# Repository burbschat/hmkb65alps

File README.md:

# HMKB 65 Alps Compatible PCB and Plate
## Case
* HMKB V1 65 AAA by Heavymetal Keyboards

## Layout
Raw data for [keyboard-layout-editor.com](http://www.keyboard-layout-editor.com):
```json
["~\n`","!\n1","@\n2","#\n3","$\n4","%\n5","^\n6","&\n7","*\n8","(\n9",")\n0","_\n-","+\n=",{w:2},"Backspace",{a:7},""],
[{a:4,w:1.5},"Tab","Q","W","E","R","T","Y","U","I","O","P","{\n[","}\n]",{w:1.5},"|\n\\",{a:7},""],
[{a:4,w:1.75},"Caps Lock","A","S","D","F","G","H","J","K","L",":\n;","\"\n'",{w:2.25},"Enter",{a:7},""],
[{a:4,w:2.25},"Shift","Z","X","C","V","B","N","M","<\n,",">\n.","?\n/",{w:1.75},"Shift",{a:7},"",""],
[{a:4,w:1.25},"Ctrl",{w:1.25},"Win",{w:1.25},"Alt",{a:7,w:6.25},"",{a:4},"Alt","Fn","Ctrl",{a:7},"","",""] 
```
Matrix position annotated version (also without label position information as this messes with scripts using the annotated version down the line):
```json
["0,0","0,1","0,2","0,3","0,4","0,5","0,6","0,7","0,8","0,9","0,10","0,11","0,12",{w:2},"0,13","0,14"],
[{w:1.5},"1,0","1,1","1,2","1,3","1,4","1,5","1,6","1,7","1,8","1,9","1,10","1,11","1,12",{w:1.5},"1,13","1,14"],
[{w:1.75},"2,0","2,1","2,2","2,3","2,4","2,5","2,6","2,7","2,8","2,9","2,10","2,11",{w:2.25},"2,13","2,14"],
[{w:2.25},"3,0","3,1","3,2","3,3","3,4","3,5","3,6","3,7","3,8","3,9","3,10",{w:1.75},"3,12","3,13","3,14"],
[{w:1.25},"4,0",{w:1.25},"4,1",{w:1.25},"4,2",{w:6.25},"4,5","4,9","4,10","4,11","4,12","4,13","4,14"]
```

Find in proper json format in `hmkb65alps.json`.
The corresponding **annotated** (i.e. which key goes where in the matrix) in
[kle-serial](https://github.com/ijprest/kle-serial) format can be found in
`hmkb65alps-annotated_kle-serial.json` (converted using
[this](https://adamws.github.io/kle-serial/)).

## PCB

### Footprints etc.
Included as submodules in `lib/`. 
* [ai03-2725's MX_V2](https://github.com/ai03-2725/MX_V2) for switch footprints
* [ai03-2725's Type-C.pretty](https://github.com/ai03-2725/Type-C.pretty) for USB-C port footprints
* [ai03-2725's random-keyboard-parts.pretty](https://github.com/ai03-2725/random-keyboard-parts.pretty) for USB-C port footprints
The MX_V2 (which also contain ALPS footprints) are fine, the other ones are not
quite to my taste.

#### 3D Models for Key Switches
Found a ALPS switch model [here](https://www.thingiverse.com/thing:3829342/files). 
Very kindly there is an scad file provided (and not just a mesh `.stl` or similar)!

### Components
#### USB-C Connector
All of the options here are selected to be hand solderable.

`Korean Hroparts Elec TYPE-C-31-M-12` Seems to be a popular choice, probably because it's dirt cheap (<20cents).
However, it's not available on DigiKey, Mouser or RS. 

`GCT` offers a series of hand solderable connectors.
[Compare them here](https://gct.co/product-compare/usb/usb4085,usb4105,usb4730,usb4800,usb4215).
Note that `USB4085` is entirely through hole, which however at the same time makes accessing the pins challenging.
For this PCB the accessible D+/D- pins were in the wrong order, which is why a different connector was used.
`USB4105` and `USB4215` seem to be essentially the same, with `USB4215` having some locating plastic pegs on the bottom.
The latter however seems not to be available at the usual vendors, so here `USB4105` is choosen as an slighly less cheap
alternative to the dirt cheep `HRO` mentioned above.
`GCT` also has very well structured documentation and links to footprints and 3d models on their website.

### `kbplacer`
Used this [Kicad Plugin](https://github.com/adamws/kicad-kbplacer) for helping
with schematic/layout generation.
There is also a script `layout2schematic.py` in the repository which was used
to generate the key matrix part of the schematic.
Technically one can also access this when the `kbplacer` python package is
installed with `python -m layout2schematic`, but in this case the dependencies
will not be automatically synchronized. The best way probably is to use a
`hatch` virtual environment. Clone the repo and make sure `hatch` is installed.
The `pyproject.toml` defines a `hatch` virtual environment for the tools. To
create it run `hatch env create tools`. To launch a shell with the environment
activated use `hatch -e tools shell`. One may also just run this right away as
this will create the environment if not present.
Btw. for some reason from the `hatch` environment `pythom -m layout2schematic`
does not seem to work, so run the script from the `tools` directory directly.
See also the [the readme file for the tools](https://github.com/adamws/kicad-kbplacer/blob/master/tools/README.md) for more information.

Note that the input `json` file is not directly what is obtained from the [keyboard layout editor](http://www.keyboard-layout-editor.com)!
Use [https://adamws.github.io/kle-serial](https://adamws.github.io/kle-serial/)
or [keyboard-tools.xyz/kle-converter](http://keyboard-tools.xyz/kle-converter)
(as the main README file notes).
In any case, the layout file must be one where the keys in the keyboard layout
editor are annotated using labels as `row,col` to designate where they will be
in the matrix.
Find annotated layout in `hmkb65alps-annotated.json`

**TLDR**: 
```
cd kicad-kbplacer
hatch run tools:layout2schematic -in ../hmkb65alps-annotated-converted.json -out ../pcb/hmkb65alps-matrix.kicad_sch
```
Creates the base matrix schematic which I then manually edited to fit my
preferences.
I load this as a hierarchical sheet into the main kicad project.
~~As I prefer to not use global labels for the rows/columns, I also manually
replace the global labels with hierarchical labels.~~
**Bad idea as this breaks the net resolving with `kbplacer` it seems :(.**
So global labels it is (I also tried if local labels work, but they dont).
TLDR: Use the matrix as generated by `layout2schematic.py`, no touchy.

#### Generating the layout
If you do not do anything funny to the generated key matrix schematic (like
trying to use hierarchical labels), assigning footprints to all parts, then
importing to the pcb layout and running the plugin should just work.

I first assign 1U switches to all of the switches, have them placed and then
adjust the longer ones (way easier than trying to figure out which switch was
where in the matrix.)

When running the plugin point *Keyboard layout file* to
`../hmkb65alps-annotated-converted.json` (or wherever the layout in the correct
format is).
With the MX-Alps hybrid footprints the diode position must be adjusted, as
otherwise it is too close to the holes in the PCB which is not good to begin
with and also will cause the automatic routing to fail.
In *Switch diodes setting* set *Position* to *Custom*. I Chose *Offset X =
7.5*, *Offset Y = -6.5*, *Orientation = -90* and *Side = back*.

Probably better use the *Relative* mode. This will result in the layout for the
first switch being replicated to the others. For some reason this however does
not seem to work for open ended tracks.

### Ideas
* Consider using chips containing multiple diodes in the same package to avoid soldering pain
    * Did not end up prusuing this
* Use Alps/MX hybrid footprints
    * Implemented!
* Consider Alps/MX hybrid plate
    * Can work but probably a bad idea as contact area of switches to plate will be very small
* Mill-Max Sockets for hot-swapping (should also work with hybrid footprints as seen in the pictures [here](https://blog.keeb.io/how-to-make-your-keyboard-hotswappable-with-mill-max-sockets/)).
    * Tried this one. The pins on Alps switches do not play nice with such sockets (they are wider than MX ones requiring quite large sockets)

## Plate
### Design
[ai03 Plate Generator](https://kbplate.ai03.com/) seems to be a well made modern solution (repository [here](https://github.com/ai03-2725/yet-another-keyboard-builder))!
Probably prefer using this over [what used to be the standard tool(?)](http://builder.swillkb.com/) to get plate hole locations
(select no outline, as the correct one is not available there), then manually
add the correct outline from the MX plate files distributed on the HMKB
discord.

**Holdup**, on closer inspection `swillkb` seems to provide [much more features](http://builder-docs.swillkb.com/features/)!
In fact one can adjust the stabilizers for specific keys using special attributes in the layout definition.
This one for example overrides the spacebar stabilizer to be of Cherry + Costar type by using `{a:7,w:6.25, _s:1}`.
```
["~\n`","!\n1","@\n2","#\n3","$\n4","%\n5","^\n6","&\n7","*\n8","(\n9",")\n0","_\n-","+\n=",{w:2},"Backspace",{a:7},""],
[{a:4,w:1.5},"Tab","Q","W","E","R","T","Y","U","I","O","P","{\n[","}\n]",{w:1.5},"|\n\\",{a:7},""],
[{a:4,w:1.75},"Caps Lock","A","S","D","F","G","H","J","K","L",":\n;","\"\n'",{w:2.25},"Enter",{a:7},""],
[{a:4,w:2.25},"Shift","Z","X","C","V","B","N","M","<\n,",">\n.","?\n/",{w:1.75},"Shift",{a:7},"",""],
[{a:4,w:1.25},"Ctrl",{w:1.25},"Win",{w:1.25},"Alt",{a:7,w:6.25, _s:1},"",{a:4},"Alt","Fn","Ctrl",{a:7},"","",""]
```
This is exactly what I need for the Tai-Hao Keycaps which have cherry type stabilizers on only the spacebar.
Seems like one can also further [specify the outline](http://builder-docs.swillkb.com/features/#custom-polygons).
If possible, defining the whole plate programatically would be cool.
Actually, we could get away without using the web interface alltogether by using [`KAD`](https://github.com/swill/kad),
the library powering [builder.swillkb.com](http://builder.swillkb.com/).

**Holdup**, but `swillkb` does not do rounded corners as I might need for a PCB plate.
So I forked ai03 Plate Generator (aka yet-another-keyboard-builder) and 
[modified the code](https://github.com/burbschat/yet-another-keyboard-builder/tree/key_specific_overrides) 
with my essentially non existent javascript knowledge, which actually worked!
It's probably not pretty or good practice though, but good enough for what I need for now.

Here is the layout that should fit for stabiliziers for the Tai-Hao Alps keycaps:
```
["~\n`","!\n1","@\n2","#\n3","$\n4","%\n5","^\n6","&\n7","*\n8","(\n9",")\n0","_\n-","+\n=",{w:2},"Backspace",{a:7},""],
[{a:4,w:1.5},"Tab","Q","W","E","R","T","Y","U","I","O","P","{\n[","}\n]",{w:1.5},"|\n\\",{a:7},""],
[{a:4,w:1.75},"Caps Lock","A","S","D","F","G","H","J","K","L",":\n;","\"\n'",{w:2.25},"Enter",{a:7},""],
[{a:4,w:2.25},"Shift","Z","X","C","V","B","N","M","<\n,",">\n.","?\n/",{w:1.75},"Shift",{a:7},"",""],
[{a:4,w:1.25},"Ctrl",{w:1.25},"Win",{w:1.25},"Alt",{a:7,w:6.25, _s:"mx-basic"},"",{a:4},"Alt","Fn","Ctrl",{a:7},"","",""]
```

I also generated the plate with flipped Alps stabilizers as 
```
["~\n`","!\n1","@\n2","#\n3","$\n4","%\n5","^\n6","&\n7","*\n8","(\n9",")\n0","_\n-","+\n=",{w:2,_rs:180},"Backspace",{a:7},""],
[{a:4,w:1.5},"Tab","Q","W","E","R","T","Y","U","I","O","P","{\n[","}\n]",{w:1.5},"|\n\\",{a:7},""],
[{a:4,w:1.75,_rs:180},"Caps Lock","A","S","D","F","G","H","J","K","L",":\n;","\"\n'",{w:2.25,_rs:180},"Enter",{a:7},""],
[{a:4,w:2.25,_rs:180},"Shift","Z","X","C","V","B","N","M","<\n,",">\n.","?\n/",{w:1.75,_rs:180},"Shift",{a:7},"",""],
[{a:4,w:1.25},"Ctrl",{w:1.25},"Win",{w:1.25},"Alt",{a:7,w:6.25, _s:"mx-basic"},"",{a:4},"Alt","Fn","Ctrl",{a:7},"","",""]
```
and `alps-aek` instead of `mx-basic` for the spacebar which I then all composed in KiCad, which was possible
as the cutouts do not overlap.
This means that I do not have to worry about the orientation of the stabilizers (some Tai-Hao keycaps 
seem to have them inversed) and can later decide if I want alps or Cherry stabilizers on the spacebar 
(Tai-Hao keycaps support those on only the spacebar but there seem to also be adapters to use Alps stabilizers).

### Material
* Try lasercutting ~1.6mm plate on the lasercutter that is avaiable at my
university (even though it is not rated to cut metal this thick)?
    * Have to source metal plates which might not be cheap in small quantities
    * Not pursued eventually.
* Order FR4 plate (i.e. just a PCB). This seems to be very reasonably priced.
Getting FR4 stock cheaper and cutting on the lasercutter appeared difficult
(could not find very cheap FR4 stock).
    * Ordering a PCB in plate size seems to cost around 3000JPY. One could also
    get an aluminum PCB for just a little more, but I don't know if an aluminum
    plate is a good idea. FR4 appeared much more sturdy to me but I did not
    make a direct comparison.
    * This is the eventually adopted option

## References
* [Masterzen's blog](https://www.masterzen.fr/2020/05/03/designing-a-keyboard-part-1/) (multiple parts)
* Artwork on the PCB is Comet from [Higgs-Tan](https://higgstan.com/)

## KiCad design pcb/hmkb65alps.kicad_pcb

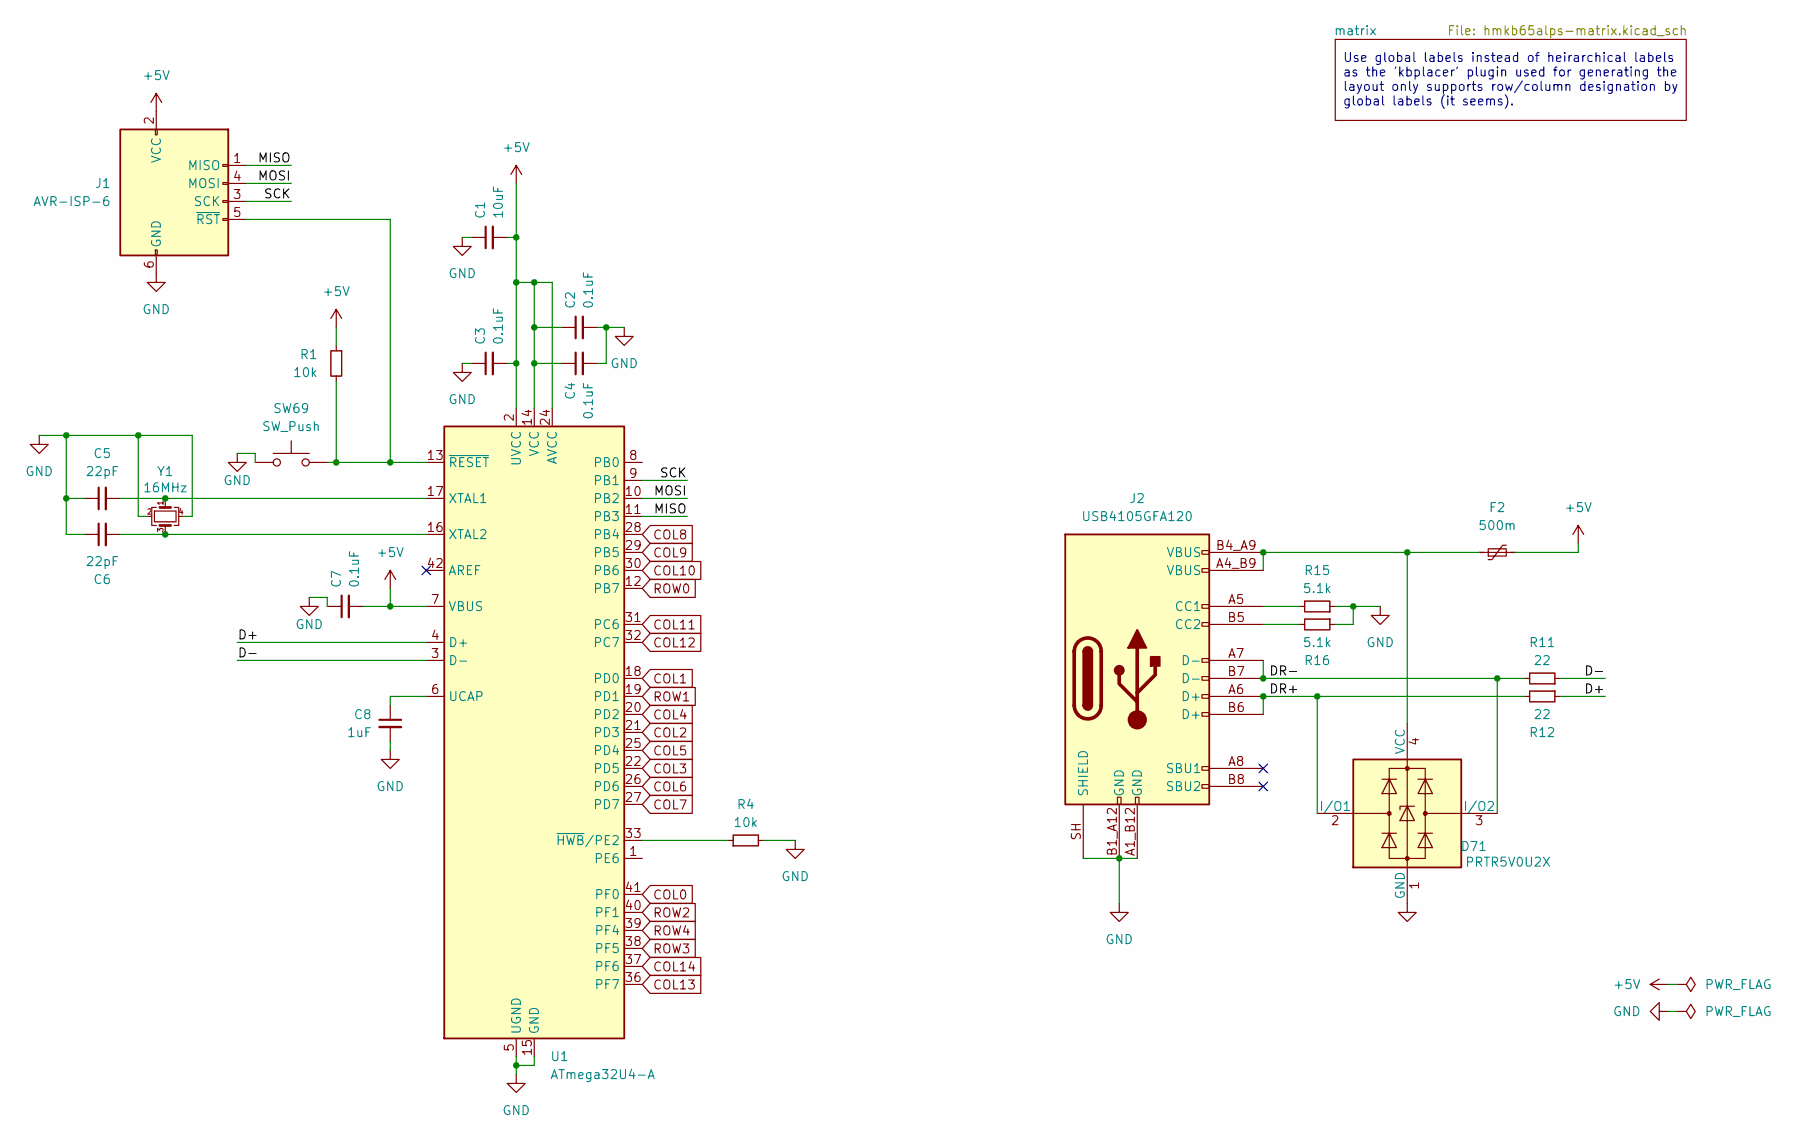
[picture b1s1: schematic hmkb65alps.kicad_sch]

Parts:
C1: 10uF; C_0805_2012Metric_Pad1.18x1.45mm_HandSolder
C2, C3, C4, C7: 0.1uF; C_0805_2012Metric_Pad1.18x1.45mm_HandSolder
C5, C6: 22pF; C_0805_2012Metric_Pad1.18x1.45mm_HandSolder
C8: 1uF; C_0805_2012Metric_Pad1.18x1.45mm_HandSolder
D71: PRTR5V0U2X; SOT-143
F2: 500m; Fuse_1206_3216Metric_Pad1.42x1.75mm_HandSolder
J1: AVR-ISP-6; IDC-Header_2x03_P2.54mm_Vertical
J2: USB4105GFA120; GCT_USB4105GFA120
R1, R4: 10k; R_0805_2012Metric_Pad1.20x1.40mm_HandSolder
R11, R12: 22; R_0805_2012Metric_Pad1.20x1.40mm_HandSolder
R15, R16: 5.1k; R_0805_2012Metric_Pad1.20x1.40mm_HandSolder
SW69: SW_Push; SW_SPST_SKQG_WithStem
U1: ATmega32U4-A; TQFP-44_10x10mm_P0.8mm
Y1: 16MHz; Crystal_SMD_3225-4Pin_3.2x2.5mm_HandSoldering

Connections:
+5V: C1.2, C2.1, C3.2, C4.1, C7.2, F2.2, J1.2 (VCC), R1.1, U1.2 (UVCC), U1.7 (VBUS), U1.14 (VCC), U1.24 (AVCC), U1.34 (VCC), U1.44 (AVCC)
/D+: R12.1, U1.4 (D+)
/D-: R11.1, U1.3 (D-)
/DR+: D71.2 (I/O1), J2.A6 (D+), J2.B6 (D+), R12.2
/DR-: D71.3 (I/O2), J2.A7 (D-), J2.B7 (D-), R11.2
/MISO: J1.1 (MISO), U1.11 (PB3)
/MOSI: J1.4 (MOSI), U1.10 (PB2)
/SCK: J1.3 (SCK), U1.9 (PB1)
COL0: U1.41 (PF0); also elsewhere on the board
COL1: U1.18 (PD0); also elsewhere on the board
COL2: U1.21 (PD3); also elsewhere on the board
COL3: U1.22 (PD5); also elsewhere on the board
COL4: U1.20 (PD2); also elsewhere on the board
COL5: U1.25 (PD4); also elsewhere on the board
COL6: U1.26 (PD6); also elsewhere on the board
COL7: U1.27 (PD7); also elsewhere on the board
COL8: U1.28 (PB4); also elsewhere on the board
COL9: U1.29 (PB5); also elsewhere on the board
COL10: U1.30 (PB6); also elsewhere on the board
COL11: U1.31 (PC6); also elsewhere on the board
COL12: U1.32 (PC7); also elsewhere on the board
COL13: U1.36 (PF7); also elsewhere on the board
COL14: U1.37 (PF6); also elsewhere on the board
GND: C1.1, C2.2, C3.1, C4.2, C5.1, C6.1, C7.1, C8.2, D71.1 (GND), J1.6 (GND), J2.A1_B12 (GND), J2.B1_A12 (GND), J2.SH (SHIELD), R4.2, R15.1, R16.1, SW69.1, U1.5 (UGND), U1.15 (GND), U1.23 (GND), U1.35 (GND), U1.43 (GND), Y1.2, Y1.4
unnamed: D71.4 (VCC), F2.1, J2.A4_B9 (VBUS), J2.B4_A9 (VBUS)
unnamed: J1.5 (~RST), R1.2, SW69.2, U1.13 (~RESET)
unnamed: J2.A5 (CC1), R15.2
unnamed: J2.B5 (CC2), R16.2
unnamed: C8.1, U1.6 (UCAP)
unnamed: C5.2, U1.17 (XTAL1), Y1.1
unnamed: C6.2, U1.16 (XTAL2), Y1.3
unnamed: R4.1, U1.33 (~HWB/PE2)
ROW0: U1.12 (PB7); also elsewhere on the board
ROW1: U1.19 (PD1); also elsewhere on the board
ROW2: U1.40 (PF1); also elsewhere on the board
ROW3: U1.38 (PF5); also elsewhere on the board
ROW4: U1.39 (PF4); also elsewhere on the board

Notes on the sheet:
Use global labels instead of heirarchical labels as the 'kbplacer' plugin used for generating the layout only supports row/column designation by global labels (it seems).

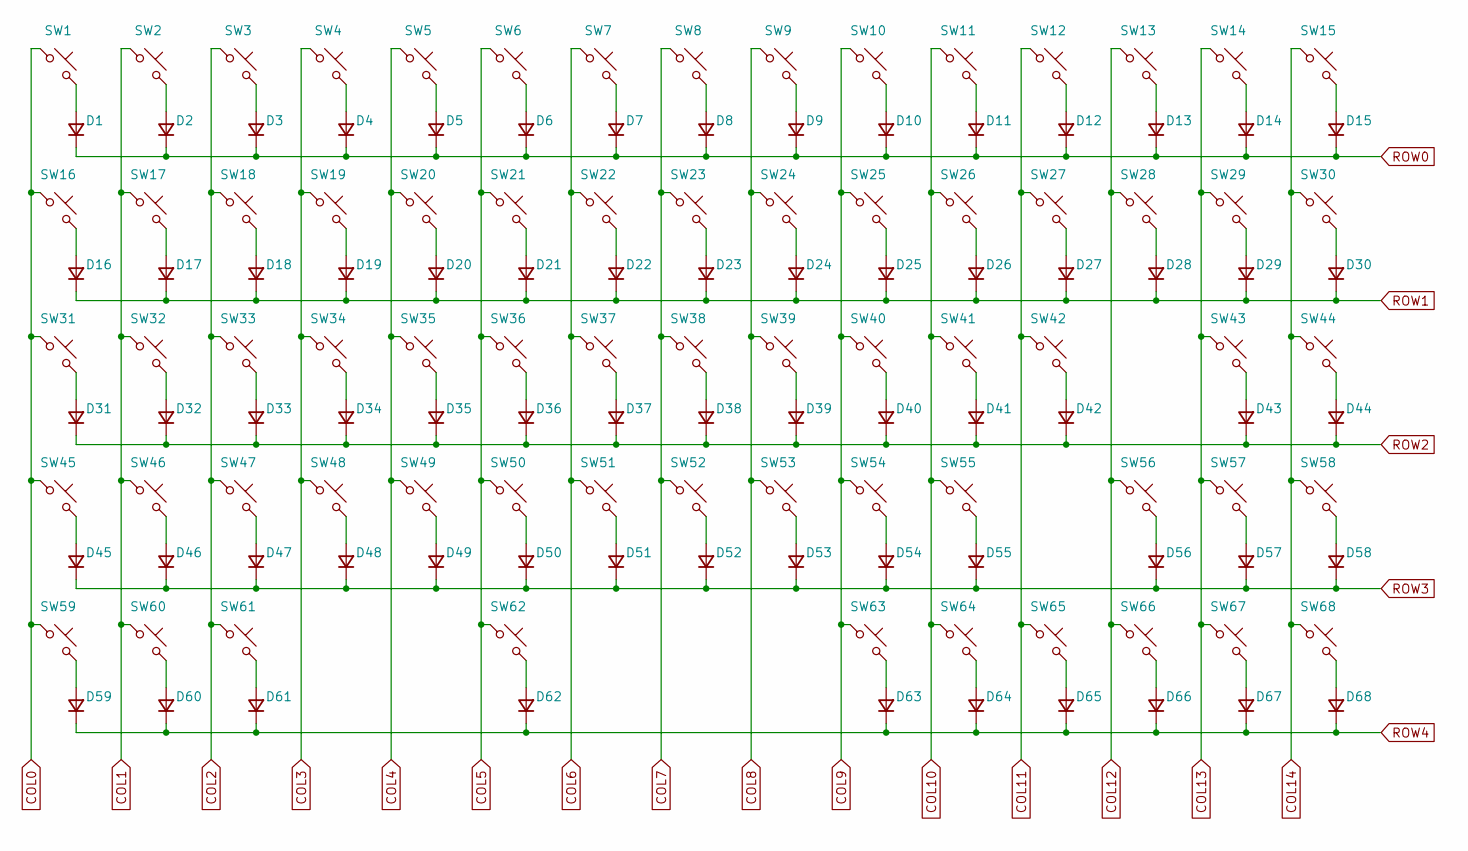
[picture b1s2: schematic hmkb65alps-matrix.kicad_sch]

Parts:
D1, D2, D3, D4, D5, D6, D7, D8, D9, D10, D11, D12, D13, D14, D15, D16, D17, D18, D19, D20, D21, D22, D23, D24, D25, D26, D27, D28, D29, D30, D31, D32, D33, D34, D35, D36, D37, D38, D39, D40, D41, D42, D43, D44, D45, D46, D47, D48, D49, D50, D51, D52, D53, D54, D55, D56, D57, D58, D59, D60, D61, D62, D63, D64, D65, D66, D67, D68: D; D_SOD-123
SW1, SW2, SW3, SW4, SW5, SW6, SW7, SW8, SW9, SW10, SW11, SW12, SW13, SW15, SW17, SW18, SW19, SW20, SW21, SW22, SW23, SW24, SW25, SW26, SW27, SW28, SW30, SW32, SW33, SW34, SW35, SW36, SW37, SW38, SW39, SW40, SW41, SW42, SW44, SW46, SW47, SW48, SW49, SW50, SW51, SW52, SW53, SW54, SW55, SW57, SW58, SW63, SW64, SW65, SW66, SW67, SW68: SW_Push; MX-Alps-Hybrid-1U
SW14: SW_Push; MX-Alps-Hybrid-2U
SW16, SW29: SW_Push; MX-Alps-Hybrid-1.5U
SW31, SW56: SW_Push; MX-Alps-Hybrid-1.75U
SW43, SW45: SW_Push; MX-Alps-Hybrid-2.25U
SW59, SW60, SW61: SW_Push; MX-Alps-Hybrid-1.25U
SW62: SW_Push; MX-Alps-Hybrid-6.25U

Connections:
COL0: SW1.1, SW16.1, SW31.1, SW45.1, SW59.1; also elsewhere on the board
COL1: SW2.1, SW17.1, SW32.1, SW46.1, SW60.1; also elsewhere on the board
COL2: SW3.1, SW18.1, SW33.1, SW47.1, SW61.1; also elsewhere on the board
COL3: SW4.1, SW19.1, SW34.1, SW48.1; also elsewhere on the board
COL4: SW5.1, SW20.1, SW35.1, SW49.1; also elsewhere on the board
COL5: SW6.1, SW21.1, SW36.1, SW50.1, SW62.1; also elsewhere on the board
COL6: SW7.1, SW22.1, SW37.1, SW51.1; also elsewhere on the board
COL7: SW8.1, SW23.1, SW38.1, SW52.1; also elsewhere on the board
COL8: SW9.1, SW24.1, SW39.1, SW53.1; also elsewhere on the board
COL9: SW10.1, SW25.1, SW40.1, SW54.1, SW63.1; also elsewhere on the board
COL10: SW11.1, SW26.1, SW41.1, SW55.1, SW64.1; also elsewhere on the board
COL11: SW12.1, SW27.1, SW42.1, SW65.1; also elsewhere on the board
COL12: SW13.1, SW28.1, SW56.1, SW66.1; also elsewhere on the board
COL13: SW14.1, SW29.1, SW43.1, SW57.1, SW67.1; also elsewhere on the board
COL14: SW15.1, SW30.1, SW44.1, SW58.1, SW68.1; also elsewhere on the board
unnamed: D1.2 (A), SW1.2
unnamed: D2.2 (A), SW2.2
unnamed: D3.2 (A), SW3.2
unnamed: D4.2 (A), SW4.2
unnamed: D5.2 (A), SW5.2
unnamed: D6.2 (A), SW6.2
unnamed: D7.2 (A), SW7.2
unnamed: D8.2 (A), SW8.2
unnamed: D9.2 (A), SW9.2
unnamed: D10.2 (A), SW10.2
unnamed: D11.2 (A), SW11.2
unnamed: D12.2 (A), SW12.2
unnamed: D13.2 (A), SW13.2
unnamed: D14.2 (A), SW14.2
unnamed: D15.2 (A), SW15.2
unnamed: D16.2 (A), SW16.2
unnamed: D17.2 (A), SW17.2
unnamed: D18.2 (A), SW18.2
unnamed: D19.2 (A), SW19.2
unnamed: D20.2 (A), SW20.2
unnamed: D21.2 (A), SW21.2
unnamed: D22.2 (A), SW22.2
unnamed: D23.2 (A), SW23.2
unnamed: D24.2 (A), SW24.2
unnamed: D25.2 (A), SW25.2
unnamed: D26.2 (A), SW26.2
unnamed: D27.2 (A), SW27.2
unnamed: D28.2 (A), SW28.2
unnamed: D29.2 (A), SW29.2
unnamed: D30.2 (A), SW30.2
unnamed: D31.2 (A), SW31.2
unnamed: D32.2 (A), SW32.2
unnamed: D33.2 (A), SW33.2
unnamed: D34.2 (A), SW34.2
unnamed: D35.2 (A), SW35.2
unnamed: D36.2 (A), SW36.2
unnamed: D37.2 (A), SW37.2
unnamed: D38.2 (A), SW38.2
unnamed: D39.2 (A), SW39.2
unnamed: D40.2 (A), SW40.2
unnamed: D41.2 (A), SW41.2
unnamed: D42.2 (A), SW42.2
unnamed: D43.2 (A), SW43.2
unnamed: D44.2 (A), SW44.2
unnamed: D45.2 (A), SW45.2
unnamed: D46.2 (A), SW46.2
unnamed: D47.2 (A), SW47.2
unnamed: D48.2 (A), SW48.2
unnamed: D49.2 (A), SW49.2
unnamed: D50.2 (A), SW50.2
unnamed: D51.2 (A), SW51.2
unnamed: D52.2 (A), SW52.2
unnamed: D53.2 (A), SW53.2
unnamed: D54.2 (A), SW54.2
unnamed: D55.2 (A), SW55.2
unnamed: D56.2 (A), SW56.2
unnamed: D57.2 (A), SW57.2
unnamed: D58.2 (A), SW58.2
unnamed: D59.2 (A), SW59.2
unnamed: D60.2 (A), SW60.2
unnamed: D61.2 (A), SW61.2
unnamed: D62.2 (A), SW62.2
unnamed: D63.2 (A), SW63.2
unnamed: D64.2 (A), SW64.2
unnamed: D65.2 (A), SW65.2
unnamed: D66.2 (A), SW66.2
unnamed: D67.2 (A), SW67.2
unnamed: D68.2 (A), SW68.2
ROW0: D1.1 (K), D2.1 (K), D3.1 (K), D4.1 (K), D5.1 (K), D6.1 (K), D7.1 (K), D8.1 (K), D9.1 (K), D10.1 (K), D11.1 (K), D12.1 (K), D13.1 (K), D14.1 (K), D15.1 (K); also elsewhere on the board
ROW1: D16.1 (K), D17.1 (K), D18.1 (K), D19.1 (K), D20.1 (K), D21.1 (K), D22.1 (K), D23.1 (K), D24.1 (K), D25.1 (K), D26.1 (K), D27.1 (K), D28.1 (K), D29.1 (K), D30.1 (K); also elsewhere on the board
ROW2: D31.1 (K), D32.1 (K), D33.1 (K), D34.1 (K), D35.1 (K), D36.1 (K), D37.1 (K), D38.1 (K), D39.1 (K), D40.1 (K), D41.1 (K), D42.1 (K), D43.1 (K), D44.1 (K); also elsewhere on the board
ROW3: D45.1 (K), D46.1 (K), D47.1 (K), D48.1 (K), D49.1 (K), D50.1 (K), D51.1 (K), D52.1 (K), D53.1 (K), D54.1 (K), D55.1 (K), D56.1 (K), D57.1 (K), D58.1 (K); also elsewhere on the board
ROW4: D59.1 (K), D60.1 (K), D61.1 (K), D62.1 (K), D63.1 (K), D64.1 (K), D65.1 (K), D66.1 (K), D67.1 (K), D68.1 (K); also elsewhere on the board

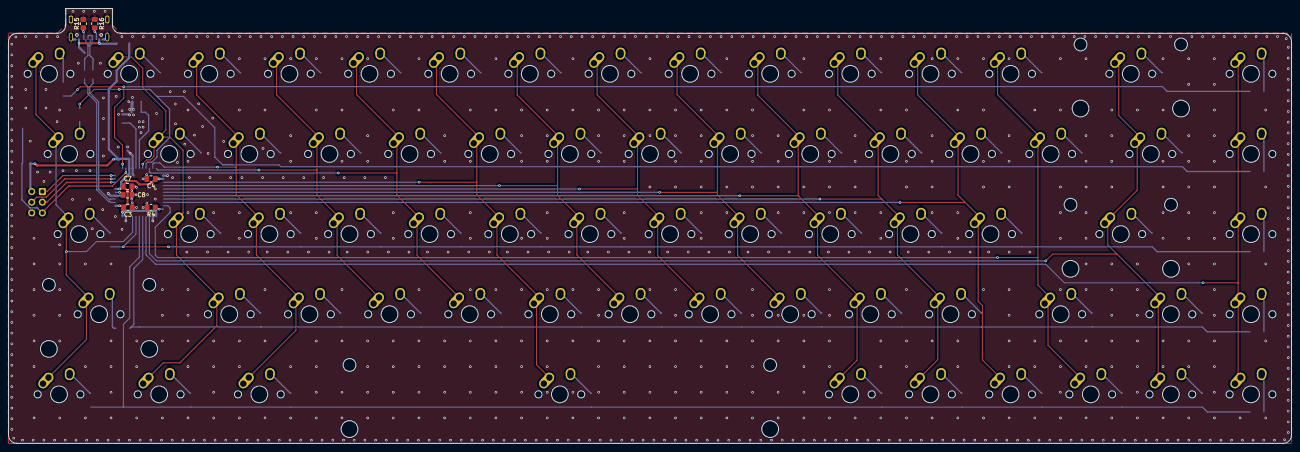
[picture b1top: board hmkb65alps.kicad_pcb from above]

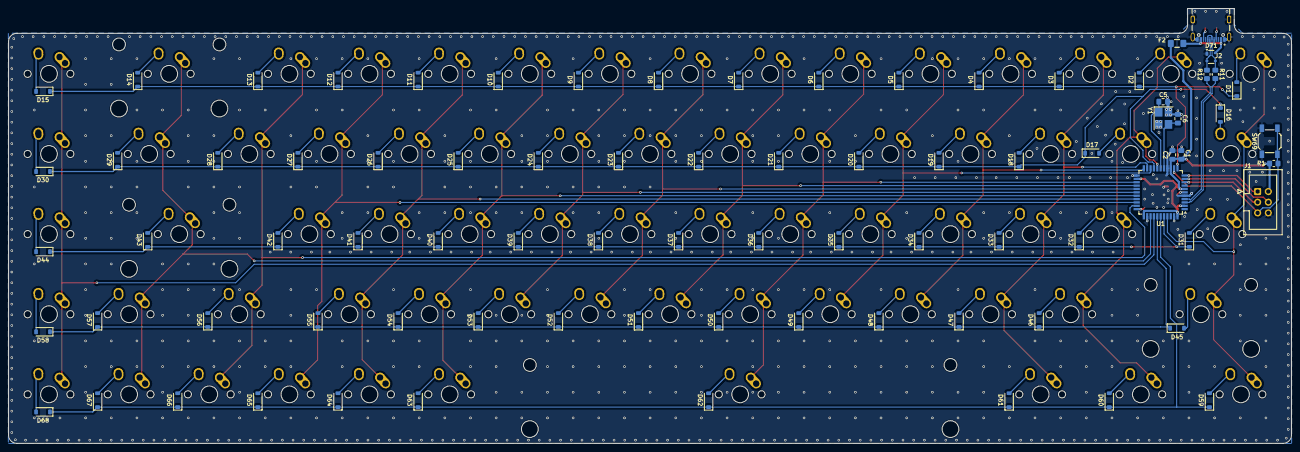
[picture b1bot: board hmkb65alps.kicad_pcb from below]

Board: 2 copper layers, 305.0 x 103.4 mm, 157 parts (82 on the bottom side), 105 nets.

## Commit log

2024-05-25 add layout files in the correct formats
    took a while to figure out the details, but the important parts should
    be noted in the README.md
2024-05-26 add submodules for switch and usb-c footprints
2024-05-26 create kicad project for pcb
    also add some of the possibly useful footprint libraries to the library
    table
2024-05-26 add further library as submodule
2024-05-26 add symbol libraries and further footprint library to tables
2024-05-26 draw mcu schematic
2024-05-26 use git lfs for 3d models (.step and .STEP so far)
2024-05-26 add USB4085-GF-A 3d model
2024-05-26 add local symbol library for project
2024-05-26 add usb-c and ISP to mcu schematic
2024-05-26 add key key matrix to schematic
2024-05-26 revert to global labels for matrix
    kbplacer does unfortunately not seem to work with local or hierarchical
    labels (which I would have prefered). So global labels it is.
    Essentially that means using the schematic generated by
    `layout2schematic.py` works fine and best.
2024-05-26 define net classes and corresponding track widths
2024-05-26 assign correct switch footprints to all switches
2024-05-26 place switches and set some design rules
2024-05-26 fix manually where the kbplace autorouter failed
2024-05-26 add missing values for oscillator capacitors
2024-05-26 sort of arrange the mcu related components
    need to get the pcb outline next to do proper positioning.
2024-05-31 adjust horizontal matrix row traces location
2024-05-31 roughly position mcu and sourrounding components
    Also change to different usbc footprint
2024-06-01 add and switch to yet a different usb-c connector
    also prepare a nicer symbol and clean up libraries
2024-06-01 set outline and fix position of mcu, connectors etc.
    next step is routing the rows/column connections to mcu
2024-06-01 begin project for prototype pcb (less keys)
2024-06-01 update switch footprint submodule to be my fork of the repo
2024-06-01 comment on footprint libraries
2024-06-01 add freecad file for plate (first test, not final at all)
2024-06-02 place most components on prototype numblock board
2024-06-02 adjust lower edge cut position for more clearance to stabilizer holes
2024-06-08 complete the prototype numpad pcb
2024-06-16 add bom related tables
2024-06-16 add updated digikey parts list
2024-06-16 rename digikey parts csv
2024-06-16 update list to actually ordered parts
2024-06-16 update some bom things
    not what I actually ordered for the most part, number of components is
    may differ.
2024-06-16 add list of parts ordered from digikey
2024-06-30 change hmkb64 -> hmkb65
    I just typoed in the very beginning and never came around to fix it.
2024-06-30 fix absolute path to footprint library
2024-06-30 create project for plate pcb and import outline from dxf
2024-07-01 notes on keyboard plate
2024-07-02 ignore plot output folder
2024-07-02 route and assign all rows/columns of the matrix
    also add some more vias where found neccessary
2024-07-02 add vias around outline
2024-07-02 add stitching vias
2024-07-03 place some more stiching vias where it appeared reasonable
2024-07-14 come up with a plate that "should" work
2024-07-14 adjust position of reset switch to line up with hole in case
2024-07-14 move components on front side where they would have interfered with switches
2024-07-14 add custom stuff on silkscreen
2024-07-14 move not so nice looking trace
2024-07-14 add some graphics to maybe put on silkscreen because why not
2024-07-14 adjust programming header silkscreen and add email
2024-07-15 stitch planes because why not and reduce copper to edge clearance
2024-07-15 further reduce copper to edge clearance
2024-07-15 add kibot configuration file
    for now just does some basic thigs I assume I'll need
2024-07-15 check DRC/ERCs and fix minor errors+warnings in ERC
2024-07-15 point submodule to my fork
    not sure what is going on. Nothing points to my fork but we still find
    the changes I made? Are the detached commits somehow included in the top
    repository?
2024-07-15 revert to branch with soldermask over via annuals on top layer
2024-07-15 adjust footprint submodule to include 3d models
    the main branch did not yet have re-generated footprints that point to
    the 3d models.
2024-07-15 fix kibot config to actually export all the layers needed
2024-07-15 finalize for production
    double check DRC/ERC etc
2024-07-15 decided against using footprints with no mask cutouts on top layer
    There is no solder mask over the holes and I'm not so sure if that could
    mean that the manufacturers will just put the mask over the hole as with
    a tented via, which would be bad. So I stick with the exposed pads on
    the front which I know work fine.
2024-07-15 add basic kibot config for pcb
2024-07-20 create plate and draw up simple case for numblock in freecad
2024-08-02 fix missing erc check in kibot config
2025-08-09 Update PCB files to v9
2025-08-09 Add htmlbom output
2025-08-09 Update plate files to v9
2025-09-06 Cleanup README
2025-09-06 Fix absolute path in fp-lib-table
2025-09-06 Remove ibom
